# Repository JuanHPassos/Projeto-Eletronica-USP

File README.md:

# Projeto-Eletronica-USP
## Projeto desenvolvido para a disciplina de Eletrônica
## Instruções:
Construção de uma fonte reficadora capaz de transformar corrente alternada de tensão eficaz de 127 volts (pico de 179,6 volts) em uma corrente contínua, com valor de tensão ajustável entre 3 e 12 volts.

Teremos a partir da tomada: tensão 127 volts, corrente alternada e frequência de 60 hz.
## Escolha dos componentes:
| Quantidade | Componentes       | Valor R$ |
|------------|-------------------|----------|
| 1          | Capacitor 680uF   | [R$ 5.80](https://produto.mercadolivre.com.br/MLB-1329526998-capacitor-eletrolitico-680uf-x-25v-105-10-pecas-_JM#position=1&search_layout=grid&type=item&tracking_id=e3802299-ff00-42ad-964e-d3a5aee62ea2)|
| 1          | Resistor 2K7 ohm  | [R$ 0.70](https://produto.mercadolivre.com.br/MLB-2715520561-100-unidades-resistor-27k-5-14w-cr25-2k7-_JM?matt_tool=14213447&matt_word=&matt_source=bing&matt_campaign=MLB_ML_BING_AO_CE-ALL-ALL_X_PLA_ALLB_TXS_ALL&matt_campaign_id=382858295&matt_ad_group=CE&matt_match_type=e&matt_network=o&matt_device=c&matt_keyword=default&msclkid=e1b9d86fc71116606eb9be032e0e646a&utm_source=bing&utm_medium=cpc&utm_campaign=MLB_ML_BING_AO_CE-ALL-ALL_X_PLA_ALLB_TXS_ALL&utm_term=4581596253419741&utm_content=CE)|
| 1          | Resistor 4K7 ohm  | [R$ 0.70](https://produto.mercadolivre.com.br/MLB-3389009219-resistor-4k7-cr25-14w-5-alta-qualidade-pacote-500-pecas-_JM#is_advertising=true&position=2&search_layout=grid&type=pad&tracking_id=d5ff520b-1146-494a-bd8a-95c6fa6acacd&is_advertising=true&ad_domain=VQCATCORE_LST&ad_position=2&ad_click_id=NDYyYmZkZDAtOWU3OC00YmM3LTgzOTAtODRhNDUyMTVjMmVm)|
| 1          | Diodo Zener (13v) | [R$ 0.70](https://produto.mercadolivre.com.br/MLB-1437492980-kit-50-pecas-diodo-zener-13v-1w-1n4743a-a-granel--_JM?matt_tool=14213447&matt_word=&matt_source=bing&matt_campaign=MLB_ML_BING_AO_CE-ALL-ALL_X_PLA_ALLB_TXS_ALL&matt_campaign_id=382858295&matt_ad_group=CE&matt_match_type=e&matt_network=o&matt_device=c&matt_keyword=default&msclkid=cd780d21d7aa10914c036b4d3e2afb26&utm_source=bing&utm_medium=cpc&utm_campaign=MLB_ML_BING_AO_CE-ALL-ALL_X_PLA_ALLB_TXS_ALL&utm_term=4581596253419739&utm_content=CE)|
| 1          | Potenciômetro 10K | [R$ 7.00](https://produto.mercadolivre.com.br/MLB-1178895152-kit-10-potenciometro-linear-10k-16mm-linear-_JM?matt_tool=14213447&matt_word=&matt_source=bing&matt_campaign=MLB_ML_BING_AO_CE-ALL-ALL_X_PLA_ALLB_TXS_ALL&matt_campaign_id=382858295&matt_ad_group=CE&matt_match_type=e&matt_network=o&matt_device=c&matt_keyword=default&msclkid=519cbb9024fb13dddea5ddfccd4e713c&utm_source=bing&utm_medium=cpc&utm_campaign=MLB_ML_BING_AO_CE-ALL-ALL_X_PLA_ALLB_TXS_ALL&utm_term=4581596253419738&utm_content=CE)|
| 1          | Ponte Retificadora| [R$ 3.90](https://produto.mercadolivre.com.br/MLB-1290426853-kit-10-ponte-retificadora-2a-1000v-original-_JM?matt_tool=14213447&matt_word=&matt_source=bing&matt_campaign=MLB_ML_BING_AO_CE-ALL-ALL_X_PLA_ALLB_TXS_ALL&matt_campaign_id=382858295&matt_ad_group=CE&matt_match_type=e&matt_network=o&matt_device=c&matt_keyword=default&msclkid=650bb0b5b40c1b56d52ed6d95e0eaf1b&utm_source=bing&utm_medium=cpc&utm_campaign=MLB_ML_BING_AO_CE-ALL-ALL_X_PLA_ALLB_TXS_ALL&utm_term=4581596253419738&utm_content=CE)|
| 1          | Led Vermelho 5mm  | [R$ 1.00](https://www.mercadolivre.com.br/led-vermelho-difuso-5mm-50-unidades-eletrnica-arduino-3v/p/MLB26787530#searchVariation=MLB26787530&position=2&search_layout=grid&type=product&tracking_id=adfecce4-4978-48c7-b7f0-c813b5bcd303)|
| 2          |Resistor 120 ohm 5W| [R$ 1.00](https://produto.mercadolivre.com.br/MLB-3518008789-47-r-ohms-10-pecas-resistor-de-carbono-5w-47r-ohms-5-_JM?matt_tool=14213447&matt_word=&matt_source=bing&matt_campaign=MLB_ML_BING_AO_CE-ALL-ALL_X_PLA_ALLB_TXS_ALL&matt_campaign_id=382858295&matt_ad_group=CE&matt_match_type=e&matt_network=o&matt_device=c&matt_keyword=default&msclkid=3c4b916e04d01b7cbaecf702ee0ca213&utm_source=bing&utm_medium=cpc&utm_campaign=MLB_ML_BING_AO_CE-ALL-ALL_X_PLA_ALLB_TXS_ALL&utm_term=4581596253419740&utm_content=CE)|
| 1          | Transistor NPN    | [R$ 2.00](https://produto.mercadolivre.com.br/MLB-1608263867-transistor-npn-tip41c-6-pecas-tip-41c-tip41-tip-41-ip41-_JM?matt_tool=14213447&matt_word=&matt_source=bing&matt_campaign=MLB_ML_BING_AO_CE-ALL-ALL_X_PLA_ALLB_TXS_ALL&matt_campaign_id=382858295&matt_ad_group=CE&matt_match_type=e&matt_network=o&matt_device=c&matt_keyword=default&msclkid=d61d18ae39b0139c4cf27ec2d34b9d83&utm_source=bing&utm_medium=cpc&utm_campaign=MLB_ML_BING_AO_CE-ALL-ALL_X_PLA_ALLB_TXS_ALL&utm_term=4581596253419738&utm_content=CE)|
| 1          | Protoboard        | [R$ 21.70](https://produto.mercadolivre.com.br/MLB-1421607788-protoboard-400-pontos-_JM?matt_tool=14213447&matt_word=&matt_source=bing&matt_campaign=MLB_ML_BING_AO_CE-ALL-ALL_X_PLA_ALLB_TXS_ALL&matt_campaign_id=382858295&matt_ad_group=CE&matt_match_type=e&matt_network=o&matt_device=c&matt_keyword=default&msclkid=95af03b37607195f2a4e65df9d116282&utm_source=bing&utm_medium=cpc&utm_campaign=MLB_ML_BING_AO_CE-ALL-ALL_X_PLA_ALLB_TXS_ALL&utm_term=4581596253419740&utm_content=CE)|
| 10         | Fios Jumper       | [R$ 7.00](https://www.mercadolivre.com.br/40-x-jumper-fio-conector-macho-macho-protoboard-20-cm/p/MLB36837941?pdp_filters=item_id:MLB4690760302#is_advertising=true&searchVariation=MLB36837941&position=1&search_layout=grid&type=pad&tracking_id=b294b6b8-0712-4527-878b-30fb19ecc216&is_advertising=true&ad_domain=VQCATCORE_LST&ad_position=1&ad_click_id=ODgwN2Y5ZWQtODU0Yi00MzY1LWIzZTktNmFhMDcwZjhiYzFj)|
| **Total**  |                   | **R$ 51,50**    |
## Componentes
1. **Transformador**: primeiro componente do circuito após a fonte de corrente alternada (tomada). Será responsável por reduzir de 127v a ddp proveninete da tomada para o valor desejado pela projeto (3-12v). O transformador escolhido é capaz de abaixar a tensão de 110 volts para 24 volts.

2. **Ponte de diodo(Ponte retificadora)**: utilizada para que o circuito seja abastecido com a corrente em ambos ciclos da corrente alternada.

3. **Capacitor**:  armazena a carga durante os ciclos da corrente alternada, liberando corrente quando a tensão interna é maior que a tensão vinda da fonte. Descarrega quando ocorre a inversão de ciclo.

4. **Diodo Zener**: regulador de tensão máxima. Somente conduz corrente quando a tensão que chegar alcança a tensão nominal do diodo, que no caso deste projeto, será 12v. Se a tensão for menor do que 12v, o Diodo não conduz e, portanto, não interfere no circuito, se for maior, deixará a corrente passar, mantendo a tensão em 12v naquele ponto. Informalmente, o diodo Zener “trava” o valor da tensão em 12v, que é exatamente o valor de tensão máximo que queremos na saída da nossa fonte.

5. **Resistores**: complementam o circuito de forma a limitar a corrente e impedindo que a corrente do circuito ultrapasse os valores limites dos componentes.

6. **Potenciometro**: resistor variável que permitirá o controle do valor da tensão resultante entre 3 e 12 volts.

7. **Transistor**: utilizado para permitir a passagem da corrente de forma ajustável.
## Imagem do Circuito

## Esquemático do Circuito - Eagle

## PCB - Eagle

## Cálculo do Capacitor

## Link do circuito no Falstad:
[Link_para_o_circuito](https://tinyurl.com/259cu76j)

## Vídeo no Youtube da fonte
[Explicação_circuito](https://youtu.be/dezJuHKXQiE)

[Funcionamento](https://youtu.be/6sgpQ-ToUSU)

## Alunos:
Juan Henriques Passos([Juan Passos](https://github.com/JuanHPassos))

Kattryel

Marcos Cota ([Marcos Cota](https://github.com/Mvcart))

Keren

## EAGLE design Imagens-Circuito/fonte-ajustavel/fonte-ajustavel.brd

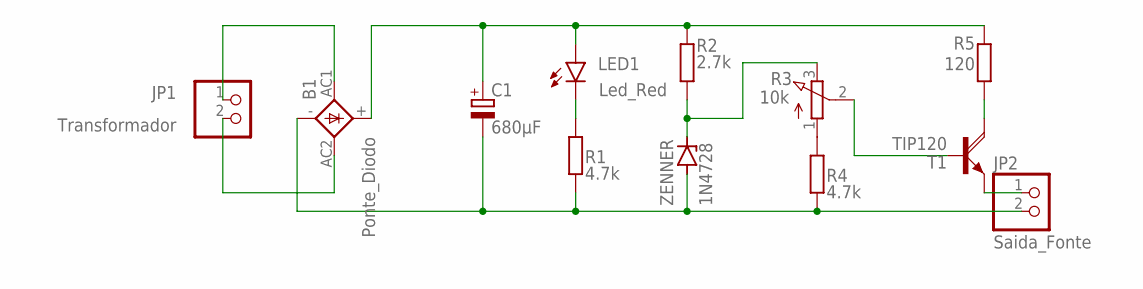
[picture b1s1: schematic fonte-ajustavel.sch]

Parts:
B1: Ponte_Diodo; 1KAB
C1: 680µF; E5-10,5
JP1: Transformador; 1X02
JP2: Saida_Fonte; 1X02
LED1: Led_Red; LED5MM
R1, R4: 4.7k; 0204/7
R2: 2.7k; 0204/7
R3: 10k; 3RP/1610N
R5: 120; 0204/7
T1: TIP120; TO220AH
ZENNER: 1N4728; DO41Z10

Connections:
unnamed: B1.AC1, JP1.1
unnamed: B1.-, C1.-, JP2.2, R1.2, R4.1, ZENNER.A
unnamed: B1.AC2, JP1.2
unnamed: R3.1 (A), R4.2
unnamed: LED1.K (C), R1.1
unnamed: R2.1, R3.3 (E), ZENNER.C
unnamed: JP2.1, T1.E
unnamed: R5.1, T1.C
unnamed: R3.2 (S), T1.B
unnamed: B1.+, C1.+, LED1.A, R2.2, R5.2

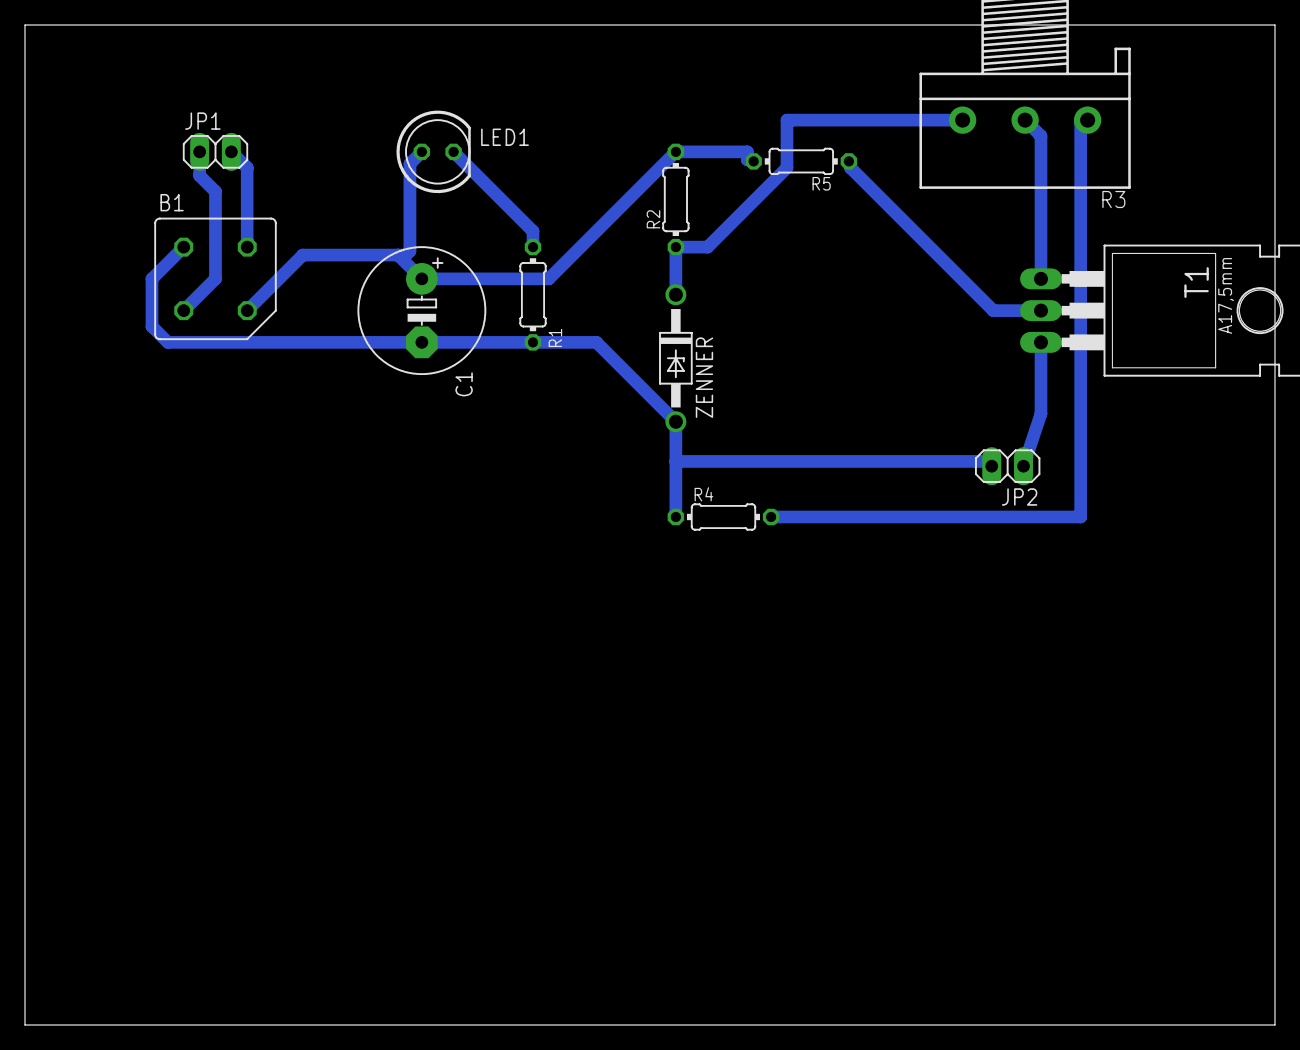
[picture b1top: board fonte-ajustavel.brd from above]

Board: 2 copper layers, 100.0 x 80.0 mm, 12 parts (0 on the bottom side), 10 nets.

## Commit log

2024-06-21 att video explicativo
2024-06-21 add eagle
2024-06-21 ajuste teorico
2024-06-25 EAGLE
2024-07-01 add keren
2024-10-25 Create LICENSE
